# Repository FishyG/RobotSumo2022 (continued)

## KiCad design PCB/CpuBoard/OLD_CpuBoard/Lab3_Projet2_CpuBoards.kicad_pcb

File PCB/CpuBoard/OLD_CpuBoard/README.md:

<pre>
   _____ _____  _    _   ____                      _     
  / ____|  __ \| |  | | |  _ \                    | |    
 | |    | |__) | |  | | | |_) | ___   __ _ _ __ __| |___ 
 | |    |  ___/| |  | | |  _ < / _ \ / _` | '__/ _` / __|
 | |____| |    | |__| | | |_) | (_) | (_| | | | (_| \__ \
  \_____|_|     \____/  |____/ \___/ \__,_|_|  \__,_|___/
</pre>
# Tutoriel Kicad TSO
Fichiers de schéma et de plan pcb pour les Cpu Boards (Propeller, Arduino et Basic Stamp 2) (Lab3_Projet2) en conception PCB Hiver 2022

<pre>
    _,--._.-,
   /\_r-,\_ )
.-.) _;='_/ (.;
 \ \'     \/S )
  L.'-. _.'|-'
 <_`-'\'_.'/
   `'-._( \
    ___   \\,      ___
    \ .'-. \\   .-'_. /
     '._' '.\\/.-'_.'
        '--``\('--'
              \\
              `\\,
                \|
Made by : - J.G-M. -
</pre>

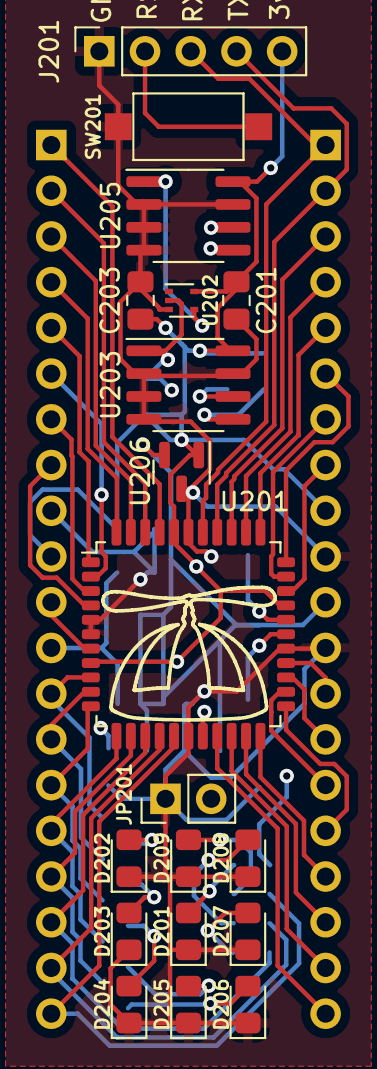
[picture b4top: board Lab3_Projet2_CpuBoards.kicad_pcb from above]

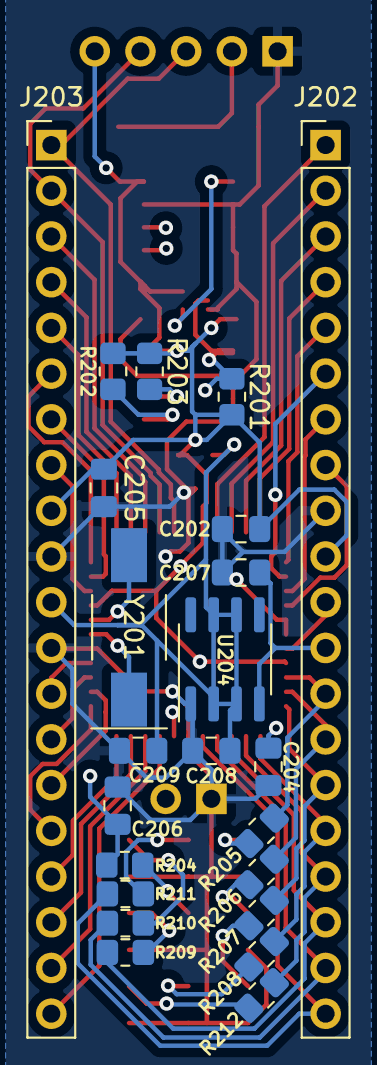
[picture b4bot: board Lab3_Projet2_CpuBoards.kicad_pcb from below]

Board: 4 copper layers, 42 parts (23 on the bottom side), 50 nets.

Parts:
C201, C202, C203, C204, C205, C206, C207, C209: 0.1µF; C_0805_2012Metric_Pad1.18x1.45mm_HandSolder
C208: 10µF; C_0805_2012Metric_Pad1.18x1.45mm_HandSolder
D201: LED_POWER; LED_0805_2012Metric_Pad1.15x1.40mm_HandSolder
D202: LED_P8; LED_0805_2012Metric_Pad1.15x1.40mm_HandSolder
D203: LED_P9; LED_0805_2012Metric_Pad1.15x1.40mm_HandSolder
D204: LED_P10; LED_0805_2012Metric_Pad1.15x1.40mm_HandSolder
D205: LED_P11; LED_0805_2012Metric_Pad1.15x1.40mm_HandSolder
D206: LED_P12; LED_0805_2012Metric_Pad1.15x1.40mm_HandSolder
D207: LED_P13; LED_0805_2012Metric_Pad1.15x1.40mm_HandSolder
D208: LED_P14; LED_0805_2012Metric_Pad1.15x1.40mm_HandSolder
D209: LED_P15; LED_0805_2012Metric_Pad1.15x1.40mm_HandSolder
J201: ProgUSB; PinSocket_1x05_P2.54mm_Vertical
J202, J203: Conn_01x20_Male; PinHeader_1x20_P2.54mm_Vertical
JP201: MemSelect; PinHeader_1x02_P2.54mm_Vertical
R201, R202, R203: 10k; R_0805_2012Metric_Pad1.20x1.40mm_HandSolder
R204, R205, R206, R207, R208, R209, R210, R211, R212: 470; R_0805_2012Metric_Pad1.20x1.40mm_HandSolder
SW201: SW_Reset; SW_SPST_CK_RS282G05A3
U201: P8X32A-Q44; LQFP-44_10x10mm_P0.8mm
U202: 74LVC1GU04; SOT-553
U203: 24LC256; SOIC-8-1EP_3.9x4.9mm_P1.27mm_EP2.41x3.81mm
U204: MC33269D-5V; SOIC-8-1EP_3.9x4.9mm_P1.27mm_EP2.29x3mm
U205: 24LC512; SOIC-8-1EP_3.9x4.9mm_P1.27mm_EP2.41x3.81mm
U206: TS3480CX33RFG; SOT-23
Y201: 5MHz; Crystal_SMD_MicroCrystal_CC1V-T1A-2Pin_8.0x3.7mm_HandSolder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

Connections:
/Propeller/3V3: C201.1, C202.1, C203.1, C204.1, C205.1, C206.1, J201.5, J202.10, J203.9, R201.1, R202.1, R203.1, R204.1, U201.8 (VDD), U201.18 (VDD), U201.30 (VDD), U201.40 (VDD), U202.5 (VCC), U203.8 (VCC), U205.8 (VCC), U206.1 (OUT)
/Propeller/5V: C208.1, C209.1, J203.11, U204.2 (VO), U204.3 (VO), U204.6 (VO), U204.7 (VO), U206.2 (IN)
/Propeller/7-12V: C207.1, J202.12, U204.4 (VI)
/Propeller/P0: J202.1, U201.41 (P0)
/Propeller/P1: J202.2, U201.42 (P1)
/Propeller/P2: J202.3, U201.43 (P2)
/Propeller/P3: J202.4, U201.44 (P3)
/Propeller/P4: J202.5, U201.1 (P4)
/Propeller/P5: J202.6, U201.2 (P5)
/Propeller/P6: J202.7, U201.3 (P6)
/Propeller/P7: J202.8, U201.4 (P7)
/Propeller/P8: J202.13, R205.1, U201.9 (P8)
/Propeller/P9: J202.14, R206.1, U201.10 (P9)
/Propeller/P10: J202.15, R207.1, U201.11 (P10)
/Propeller/P11: J202.16, R208.1, U201.12 (P11)
/Propeller/P12: J202.17, R212.1, U201.13 (P12)
/Propeller/P13: J202.18, R209.1, U201.14 (P13)
/Propeller/P14: J202.19, R210.1, U201.15 (P14)
/Propeller/P15: J202.20, R211.1, U201.16 (P15)
/Propeller/P16: J203.20, U201.19 (P16)
/Propeller/P17: J203.19, U201.20 (P17)
/Propeller/P18: J203.18, U201.21 (P18)
/Propeller/P19: J203.17, U201.22 (P19)
/Propeller/P20: J203.16, U201.23 (P20)
/Propeller/P21: J203.15, U201.24 (P21)
/Propeller/P22: J203.14, U201.25 (P22)
/Propeller/P23: J203.13, U201.26 (P23)
/Propeller/P24: J203.8, U201.31 (P24)
/Propeller/P25: J203.7, U201.32 (P25)
/Propeller/P26: J203.6, U201.33 (P26)
/Propeller/P27: J203.5, U201.34 (P27)
/Propeller/P28_SCL: J203.4, R203.2, U201.35 (P28), U203.6 (SCL), U205.6 (SCL)
/Propeller/P29_SDA: J203.3, R202.2, U201.36 (P29), U203.5 (SDA), U205.5 (SDA)
/Propeller/P30_TX: J201.4, J203.2, U201.37 (P30)
/Propeller/P31_RX: J201.3, J203.1, U201.38 (P31)
/Propeller/Reset: J201.2, J202.11, SW201.2, U201.7 (~RES)
GND: C201.2, C202.2, C203.2, C204.2, C205.2, C206.2, C207.2, C208.2, C209.2, D201.1 (K), D202.1 (K), D203.1 (K), D204.1 (K), D205.1 (K), D206.1 (K), D207.1 (K), D208.1 (K), D209.1 (K), J201.1, J202.9, J203.10, J203.12, JP201.1 (A), SW201.1, U201.5 (VSS), U201.6 (~BOE), U201.17 (VSS), U201.27 (VSS), U201.39 (VSS), U202.3 (GND), U203.2 (A1), U203.3 (A2), U203.4 (GND), U203.7 (WP), U204.1 (GND), U205.2 (A1), U205.3 (A2), U205.4 (GND), U205.7 (WP), U206.3 (GND)
unnamed: D201.2 (A), R204.2
unnamed: D202.2 (A), R205.2
unnamed: D203.2 (A), R206.2
unnamed: D204.2 (A), R207.2
unnamed: D205.2 (A), R208.2
unnamed: D206.2 (A), R212.2
unnamed: D207.2 (A), R209.2
unnamed: D208.2 (A), R210.2
unnamed: D209.2 (A), R211.2
unnamed: JP201.2 (B), R201.2, U202.2, U203.1 (A0)
unnamed: U201.28 (XI), Y201.1
unnamed: U201.29 (XO), Y201.2
unnamed: U202.4, U205.1 (A0)

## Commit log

2022-08-25 test
2022-08-25 bozopack
2022-08-25 Added Datasheet + PCB
2022-08-25 Updated parts
2022-08-25 no message
2022-08-25 Updated parts list
2022-09-01 Added datasheet + Kicad modif
2022-09-01 Finalized both power supply
2022-09-01 Version 1.0
2022-09-08 1.2 PCB
2022-09-08 1.4 Carte mere
2022-09-11 1.5 PCB
2022-09-11 Fixed Zach's Stuff
2022-09-11 added lib for tcrt5000
2022-09-11 fixed lib for tcrt5000
2022-09-11 fixed lib for tcrt5000 v2
2022-09-11 Delete TCRT5000 directory
    Not needed
2022-09-13 Modif PCB + Datasheet
2022-09-13 Modif PCB + Datasheet v2
2022-09-15 New Revision
2022-09-15 Added .gitignore
2022-09-15 2.0 alabama
2022-09-15 2.1 Missouri
2022-09-15 2.2 Florida
2022-09-16 Fixed Zach's errors :/ smh
2022-09-16 Finished v0.1
2022-09-22 Documentation
2022-09-23 Documentation annexe
2022-09-25 Completed the power supply part
2022-09-25 Documentation V1.0 Final
2022-10-06 added 3D parts + final version
2022-11-24 Added the code
2022-12-01 Updated code and 3d files
2022-12-05 Send TCP traffic to the serial port 1
2022-12-09 Added the part to read from the second serial port
2022-12-15 Cool Shit
2022-12-21 Zachary Code
2022-12-24 Added all the code (xbox360 controller + Robot Sumo + robot.sh)
